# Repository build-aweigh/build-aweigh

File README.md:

Aweigh

Royal College of Art & Imperial College, 2018

States Lee, Sam Iliffe, Keren Zhang, Flora Weil

Aweigh is a non-satellite based navigation alternative, inspired by the polarised vision of insects and ancient celestial navigation. 
This repository contains all the files necessary for building a device. It is currently subject to modifications.

The team is working on increasing the resolution of the device and developing a better distribution platform. 
Most of the files included here are still under construction. Aweigh users are invited to contribute and share their ideas, hacks, and 
improvements in this repository.

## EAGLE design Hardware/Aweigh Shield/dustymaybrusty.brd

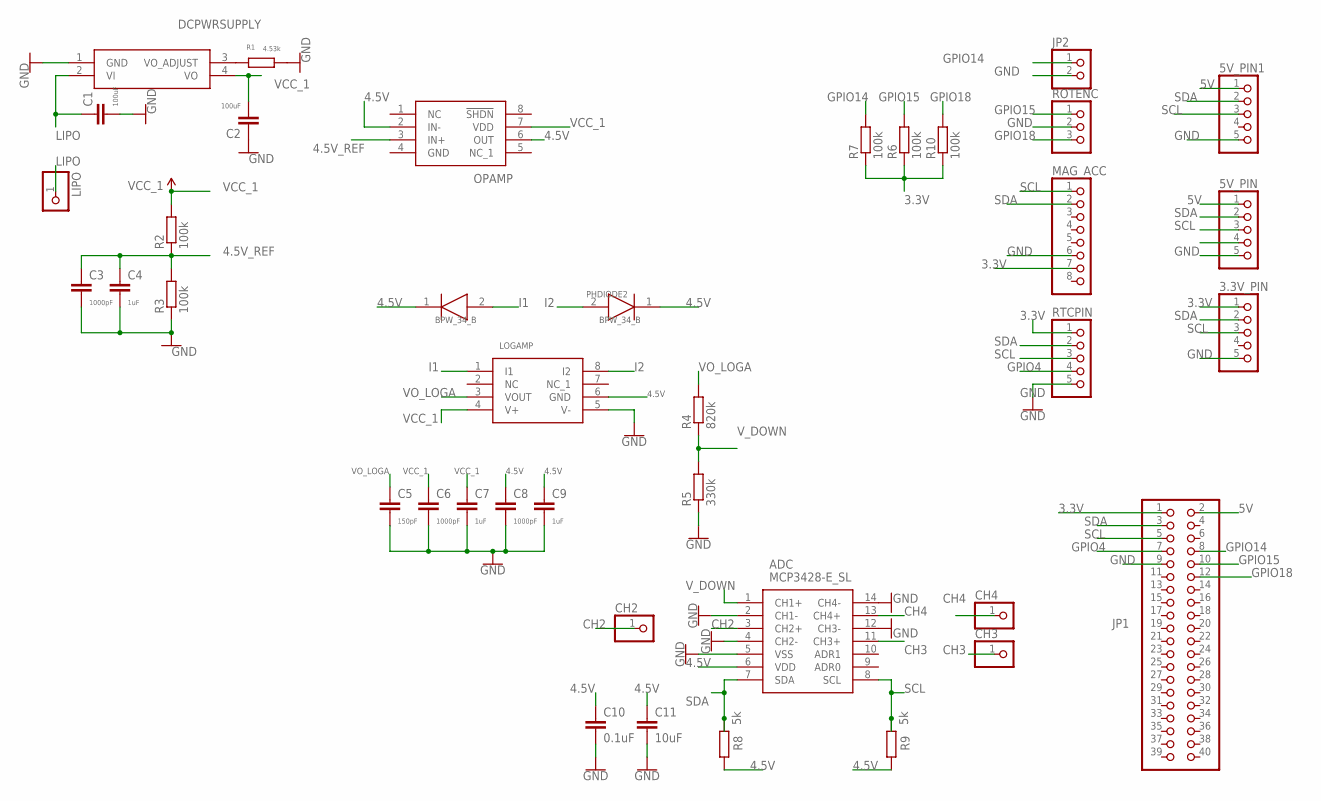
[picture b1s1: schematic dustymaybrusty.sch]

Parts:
3.3V_PIN, 5V_PIN, 5V_PIN1: PINHD-1X5; 1X05
ADC: MCP3428-E_SL; SOIC127P600X175-14N
C1, C2: 100uF; C1206
C3, C6, C8: 1000pF; C1206
C4, C7, C9: 1uF; C1206
C5: 150pF; C1206
C10: 0.1uF; C1206
C11: 10uF; C1206
CH2, CH3, CH4: PINHD-1X1; 1X01
DCPWRSUPPLY: PTN04050CAD; EUU(R-PDSS-T4)
JP1: PINHD-2X20; 2X20
JP2: PINHD-1X2; 1X02
LIPO: PINHD-1X1; 1X01
LOGAMP: LOG104AID; SOIC127P600X175-8N
MAG_ACC: PINHD-1X8; 1X08
OPAMP: TLV2370IP; DIP794W53P254L959H508Q8N
PHDIODE1, PHDIODE2: BPW_34_B; BPW34B
R1: 4.53k; R1206
R2, R3, R6, R7, R10: 100k; R1206
R4: 820k; R1206
R5: 330k; R1206
R8, R9: 5k; R1206
ROTENC: PINHD-1X3; 1X03
RTCPIN: PINHD-1X5; 1X05

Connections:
3.3V: 3.3V_PIN.1, JP1.1, MAG_ACC.7, R6.1, R7.1, R10.1, RTCPIN.1
4.5V: ADC.6 (VDD), C8.1, C9.1, C10.1, C11.1, LOGAMP.6 (GND), OPAMP.2 (IN-), OPAMP.6 (OUT), PHDIODE1.1 (K), PHDIODE2.1 (K), R8.1, R9.1
4.5V_REF: C3.1, C4.1, OPAMP.3 (IN+), R2.1, R3.2
5V: 5V_PIN.1, 5V_PIN1.1, JP1.2
CH2: ADC.3 (CH2+), CH2.1
CH3: ADC.11 (CH3+), CH3.1
CH4: ADC.13 (CH4+), CH4.1
GND: 3.3V_PIN.5, 5V_PIN.5, 5V_PIN1.5, ADC.2 (CH1-), ADC.4 (CH2-), ADC.5 (VSS), ADC.12 (CH3-), ADC.14 (CH4-), C1.2, C2.1, C3.2, C4.2, C5.2, C6.2, C7.2, C8.2, C9.2, C10.2, C11.2, DCPWRSUPPLY.1 (GND), JP1.9, JP2.2, LOGAMP.5 (V-), MAG_ACC.6, OPAMP.4 (GND), R1.1, R3.1, R5.1, ROTENC.2, RTCPIN.5
GPIO4: JP1.7, RTCPIN.4
GPIO14: JP1.8, JP2.1, R7.2
GPIO15: JP1.10, R6.2, ROTENC.1
GPIO18: JP1.12, R10.2, ROTENC.3
I1: LOGAMP.1 (I1), PHDIODE1.2 (A)
I2: LOGAMP.8 (I2), PHDIODE2.2 (A)
LIPO: C1.1, DCPWRSUPPLY.2 (VI), LIPO.1
unnamed: DCPWRSUPPLY.3 (VO_ADJUST), R1.2
SCL: 3.3V_PIN.3, 5V_PIN.3, 5V_PIN1.3, ADC.8 (SCL), JP1.5, MAG_ACC.1, R9.2, RTCPIN.3
SDA: 3.3V_PIN.2, 5V_PIN.2, 5V_PIN1.2, ADC.7 (SDA), JP1.3, MAG_ACC.2, R8.2, RTCPIN.2
VCC_1: C2.2, C6.1, C7.1, DCPWRSUPPLY.4 (VO), LOGAMP.4 (V+), OPAMP.7 (VDD), R2.2
VO_LOGA: C5.1, LOGAMP.3 (VOUT), R4.2
V_DOWN: ADC.1 (CH1+), R4.1, R5.2

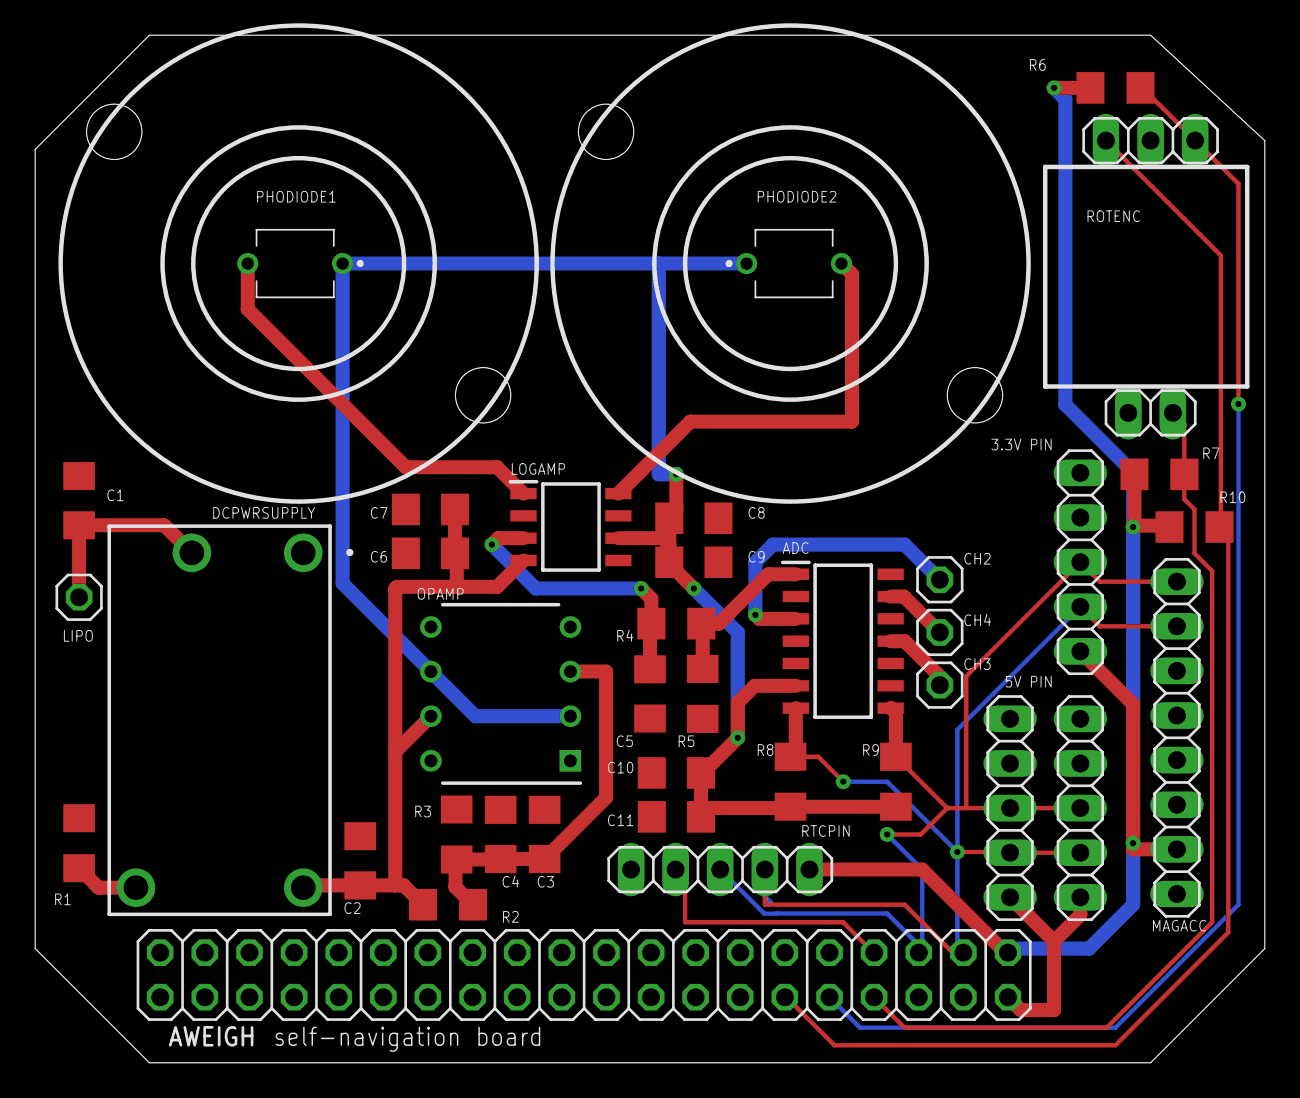
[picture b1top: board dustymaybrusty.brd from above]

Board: 2 copper layers, 70.0 x 58.5 mm, 39 parts (0 on the bottom side), 21 nets.

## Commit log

2019-01-16 Add folders
2019-01-16 Add files
2019-01-18 Add new files
2019-03-31 Create images

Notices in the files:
parts and their libraries:
SparkFun-PowerSymbols: Licensing: Creative Commons ShareAlike 4.0 International - https://creativecommons.org/licenses/by-sa/4.0
